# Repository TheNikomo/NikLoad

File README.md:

# Licensing

The hardware design files are covered under Creative Commons Attribution-ShareAlike 4.0 International (CC-BY-SA)

The software will probably end up under GPLv3 - will look into that after hardware exists

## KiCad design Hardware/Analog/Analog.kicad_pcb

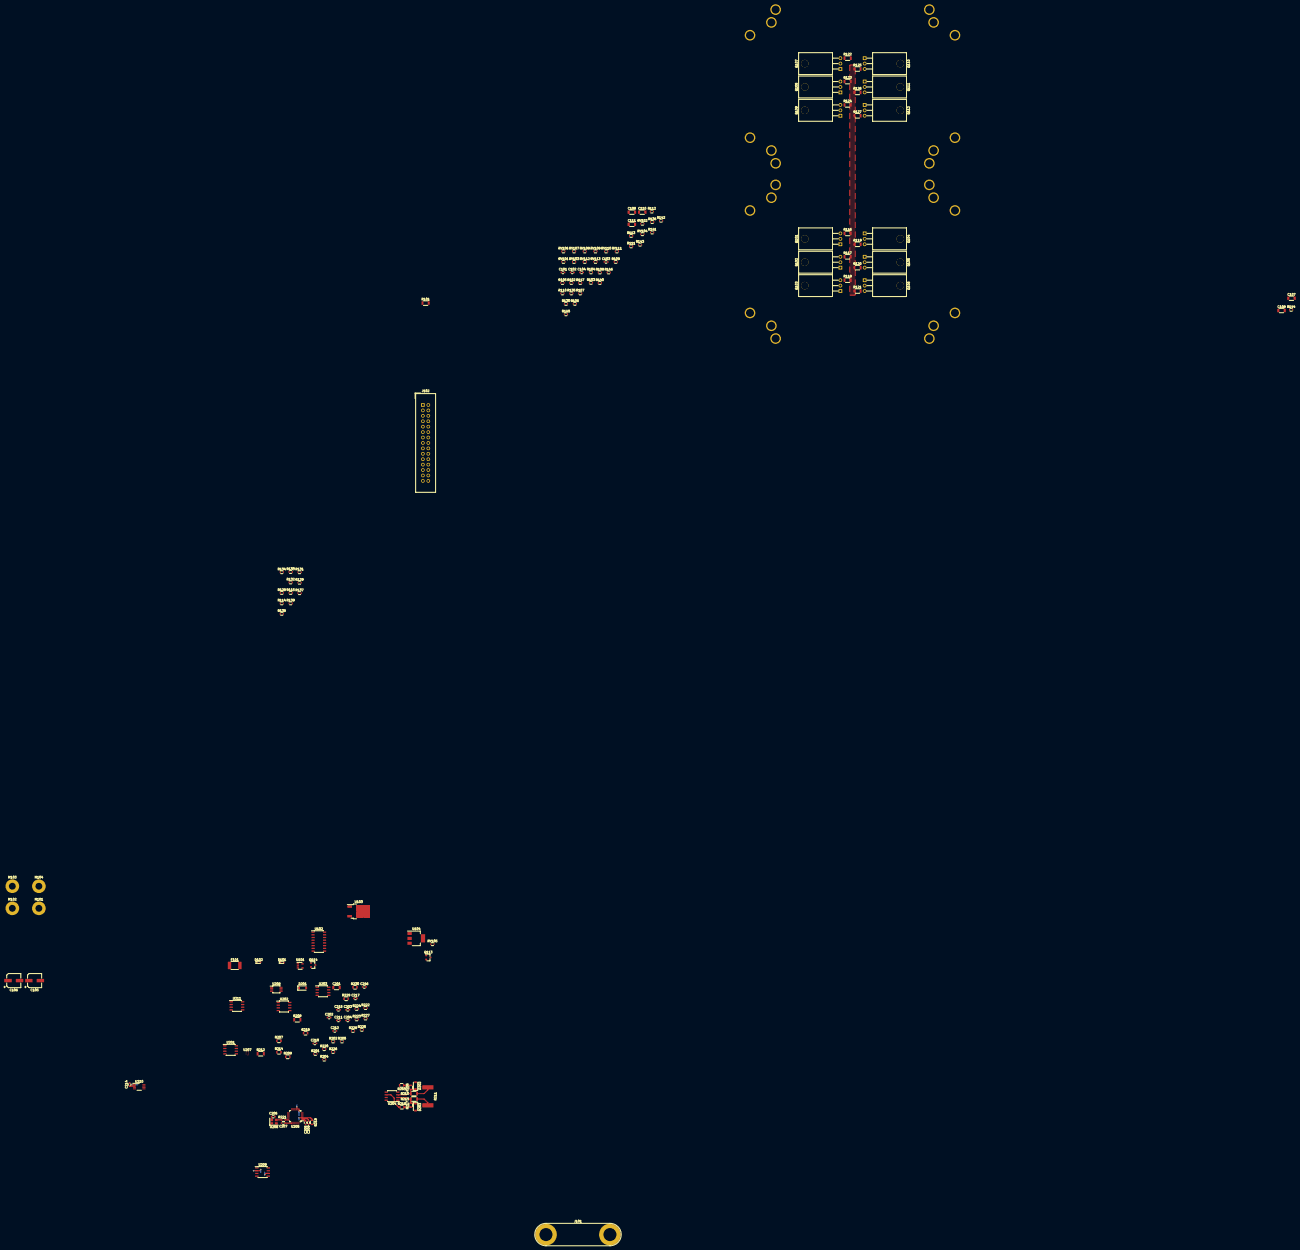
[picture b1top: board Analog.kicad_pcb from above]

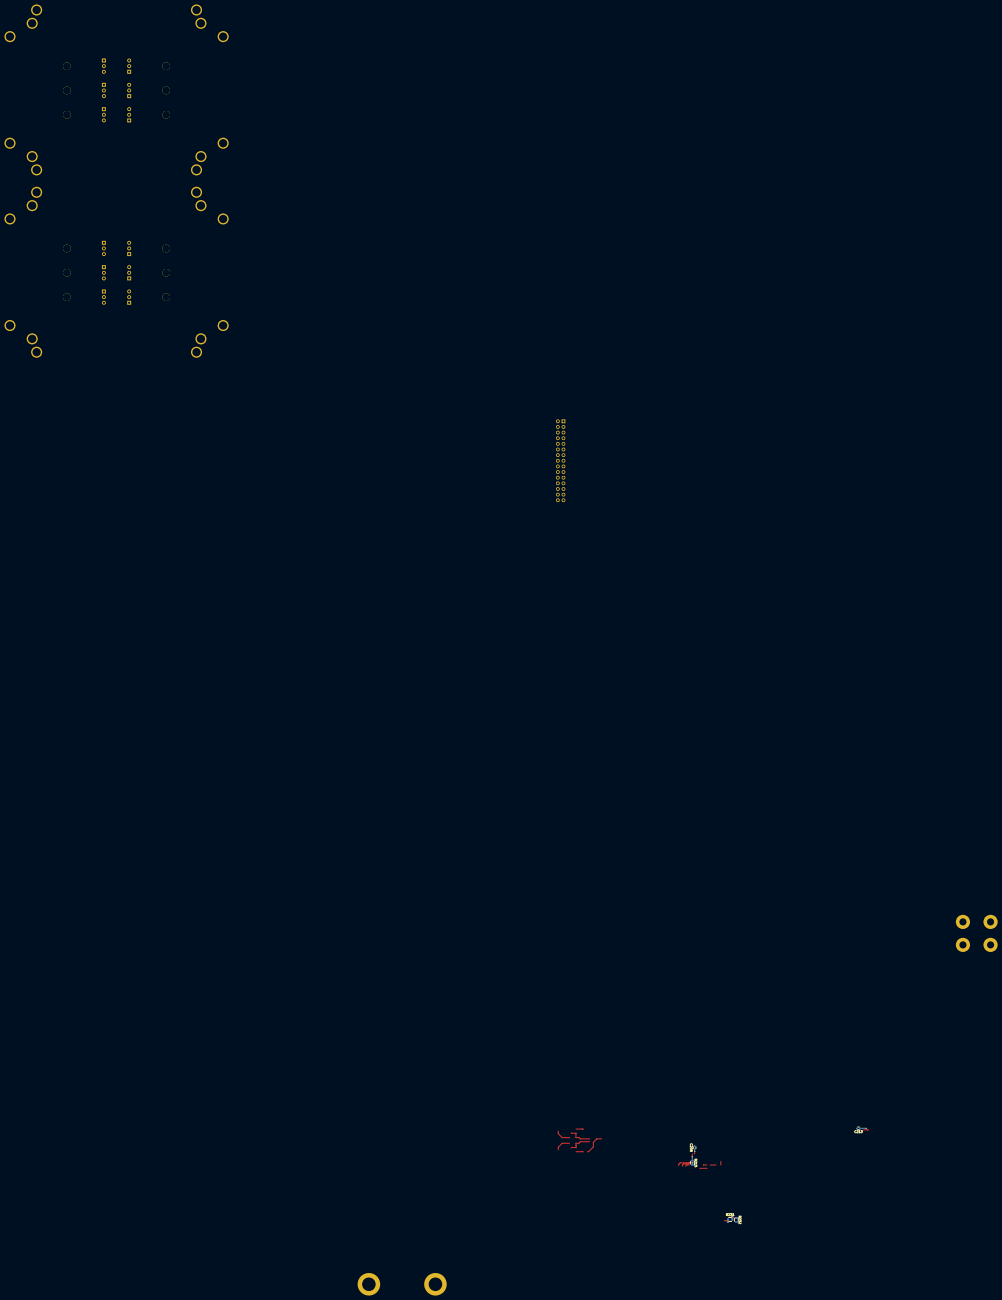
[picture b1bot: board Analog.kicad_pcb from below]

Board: 2 copper layers, 161 parts (5 on the bottom side), 112 nets.

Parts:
C101, C104, C206, C210, C211, C212, C213, C214, C215, C216, C217: 0.1µF; C_0603
C102, C202, C203, C204, C205, C207, C208, C209: 1µF; C_0603
C103: 100pF; C_0603
C105, C106: 150µF; CP_Elec_6.3x7.7
C107, C108, C109, C110, C111, C201: 10µF; C_1206
D101, D102: APG1608ZGCK; LED_0603
D201, D202, D203: BAT46WQ-7-F; D_SOD-123
F101: 16V 1.1A 1812; R_1812
J101: Pomona 4mm 30A connector; Banana_Jack_2Pin
J102: 02x15 IDC; IDC-Header_2x15_P2.54mm_Vertical
M101, M102, M103, M104: MOUNTING_HOLE; MountingHole_3.2mm_M3_Pad
Q101, Q102, Q103, Q104, Q105, Q106, Q107, Q108, Q109, Q110, Q111, Q112: PHP23NQ11T; TO-220_Horizontal
Q113, Q114: 2N7002; SOT-23
R101, R210, R213: 1k; R_1206
R102, R103, R104, R105, R106, R107, R108, R109, R110, R111, R112, R113, R146, R147: 100; R_0603
R114: 100k; R_0603
R115, R128, R129, R130, R131, R132, R133, R134, R135, R144, R145, R221: 33; R_0603
R116, R117, R118, R119, R120, R121, R122, R123, R124, R125, R126, R127: 0R02; R_1206
R136, R137, R138, R139, R140, R141, R142, R143, R201, R202, R204, R205, R222, R223, R224, R226, R227, R228: 51k1; R_0603
R203, R206, R207, R209, R214, R215, R216, R217, R218, R219, R229, R230, R231, R232: 20k; R_0805
R208: 990k; R_1206
R211: 2mOhm; R_3920
R212: 41.2k; R_1206
R220: 10k; R_0603
R225: 60k4; R_0603
RV101, RV102, RV103, RV104, RV105, RV106, RV107, RV108, RV109, RV110, RV111, RV112, RV113: 5V; R_0603
U101: OPA180; SOT-23-5
U102: 74HC595; SOIC-16_3.9x9.9mm_Pitch1.27mm
U103: NCP1117DT50G; TO-252-2
U104: SPX1117-33; SOT-223-3_TabPin2
U201, U202, U203, U204, U209: OPA388; SOIC-8_3.9x4.9mm_Pitch1.27mm
U205: ADS127L01; LQFP-32_5x5mm_Pitch0.5mm
U206: TXETCLSANF-16.384MHz; Crystal_SMD_3225-4pin_3.2x2.5mm
U207: NX3L4357
U208: MCP4921T-E/MS; MSOP-8_3x3mm_Pitch0.65mm
U210: DAC8560; VSSOP-8_3.0x3.0mm_Pitch0.65mm
U211: MAX6126AASA25+; SOIC-8_3.9x4.9mm_Pitch1.27mm

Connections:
+3V3: C104.1, C111.1, C202.1, C203.1, C204.1, C206.1, C210.1, C212.1, C213.1, R136.1, R138.1, R140.1, R142.1, R201.1, R202.2, U102.10, U102.16, U104.2, U205.6, U205.27, U205.32, U206.4, U207.10, U208.1, U210.1
+5V: C109.1, C110.1, R146.2, R147.2, U103.2, U104.3, U201.7, U202.7, U203.7, U204.7, U209.7
+12V: C101.1, C102.1, C105.1, C106.1, C107.1, C108.1, C215.1, F101.1, U101.5, U103.3, U211.2
/CurrentSense: R216.1, R229.2, U101.3, U204.6
/DUT+: J101.1, Q101.2, Q101.4, Q102.2, Q102.4, Q103.2, Q103.4, Q104.2, Q104.4, Q105.2, Q105.4, Q106.2, Q106.4, Q107.2, Q107.4, Q108.2, Q108.4, Q109.2, Q109.4, Q110.2, Q110.4, Q111.2, Q111.4, Q112.2, Q112.4, R208.1
/Measurement/ADC_INPUT: U205.4, U207.3
/Measurement/DAC8560: U207.8, U209.3, U210.3, U210.4
/Measurement/DUT-: J101.2, R211.2, R212.2, R213.1
/Measurement/FILTER0: R137.1, U205.13
/Measurement/FILTER1: R139.2, U205.12
/Measurement/OSR0: R141.2, U205.16
/Measurement/OSR1: R143.2, U205.15
/Measurement/Offset_DAC: C211.1, U201.3, U202.3, U208.8
/Measurement/Offset_LDAC: R145.1, RV110.1, U208.5
/Measurement/S0: U102.4, U207.1
/Measurement/S1: U102.5, U207.2
/Measurement/SPI0_CE0: R132.1, RV104.1, U205.23
/Measurement/SPI0_CLK: R130.1, RV101.1, U205.22
/Measurement/SPI0_MISO: R128.2, U205.20
/Measurement/SPI0_MOSI: R131.1, RV102.1, U205.21
/Measurement/SPI1_CE0: R135.1, RV108.1, U210.5
/Measurement/SPI1_CE1: R144.1, RV109.1, U208.2
/Measurement/SPI1_CLK: R133.1, RV106.1, U208.3, U210.6
/Measurement/SPI1_MOSI: R134.1, RV107.1, U208.4, U210.7
/Measurement/SenseResistor: R116.2, R117.2, R118.2, R119.2, R120.2, R121.2, R122.2, R123.2, R124.2, R125.2, R126.2, R127.2, R210.2, R211.1
/Measurement/VoltageSense: R214.1, U203.6, U207.9
/Measurement/Vref: C201.2, C214.1, C217.1, R215.2, U205.9, U208.6, U210.2, U211.6, U211.7
/Measurement/~DRDY~/FSYNC: R129.2, U205.19
/Setpoint: R101.1, R231.1, U209.6
Earth: C101.2, C102.2, C104.2, C105.2, C106.2, C107.2, C108.2, C109.2, C110.2, C111.2, C201.1, C202.2, C203.2, C204.2, C205.2, C206.2, C207.2, C208.2, C209.2, C210.2, C211.2, C212.2, C213.2, C214.2, C215.2, C216.2, C217.2, D201.2, D202.2, D203.2, J102.2, J102.4, J102.6, J102.8, J102.10, J102.12, J102.14, J102.16, J102.18, J102.20, J102.22, J102.24, J102.26, J102.28, J102.30, M101.1, M102.1, M103.1, M104.1, Q113.2, Q114.2, R114.2, R218.2, R219.2, R220.2, R225.2, R226.1, R227.1, R228.1, R230.1, R232.2, RV101.2, RV102.2, RV103.2, RV104.2, RV105.2, RV106.2, RV107.2, RV108.2, RV109.2, RV110.2, RV111.2, RV112.2, RV113.2, U101.2, U102.8, U102.13, U103.1, U104.1, U201.4, U202.4, U203.4, U204.4, U205.5, U205.10, U205.18, U205.26, U205.31, U206.2, U207.4, U207.5, U208.7, U209.4, U210.8, U211.3, U211.4
unnamed: C103.1, R115.1
unnamed: C103.2, R102.2, R103.2, R104.2, R105.2, R106.2, R107.2, R108.2, R109.2, R110.2, R111.2, R112.2, R113.2, R114.1, U101.1
unnamed: C205.1, U205.1
unnamed: C207.1, U205.25
unnamed: C208.1, U205.11
unnamed: C209.1, U205.2
unnamed: C216.1, U211.1
unnamed: D101.1, Q113.3
unnamed: D101.2, R146.1
unnamed: D102.1, Q114.3
unnamed: D102.2, R147.1
unnamed: D201.1, R207.2, R209.2, U203.3
unnamed: D202.1, R206.1, R210.1, U204.3
unnamed: D203.1, R213.2, R217.2, U204.2
unnamed: F101.2, J102.1, J102.3
unnamed: J102.5, R130.2
unnamed: J102.7, R131.2
unnamed: J102.9, R128.1, RV103.1
unnamed: J102.11, R132.2
unnamed: J102.13, R129.1, RV105.1
unnamed: J102.15, R133.2
unnamed: J102.17, R134.2
unnamed: J102.19, R135.2
unnamed: J102.21, R144.2
unnamed: J102.23, R145.2
unnamed: J102.25, RV113.1, U102.11
unnamed: J102.27, RV112.1, U102.14
unnamed: J102.29, RV111.1, U102.12
unnamed: Q101.1, R102.1
unnamed: Q101.3, R116.1
unnamed: Q102.1, R103.1
unnamed: Q102.3, R117.1
unnamed: Q103.1, R104.1
unnamed: Q103.3, R118.1
unnamed: Q104.1, R105.1
unnamed: Q104.3, R119.1
unnamed: Q105.1, R106.1
unnamed: Q105.3, R120.1
unnamed: Q106.1, R107.1
unnamed: Q106.3, R121.1
unnamed: Q107.1, R108.1
unnamed: Q107.3, R122.1
unnamed: Q108.1, R109.1
unnamed: Q108.3, R123.1
unnamed: Q109.1, R110.1
unnamed: Q109.3, R124.1
unnamed: Q110.1, R111.1
unnamed: Q110.3, R125.1
unnamed: Q111.1, R112.1
unnamed: Q111.3, R126.1
unnamed: Q112.1, R113.1
unnamed: Q112.3, R127.1
unnamed: Q113.1, U102.6
unnamed: Q114.1, U102.7
unnamed: R101.2, R115.2, U101.4
unnamed: R136.2, R137.2, U102.15
unnamed: R138.2, R139.1, U102.1
unnamed: R140.2, R141.1, U102.2
unnamed: R142.2, R143.1, U102.3
unnamed: R201.2, R204.2
unnamed: R202.1, R205.1
unnamed: R203.1, R206.2
unnamed: R203.2, U202.2, U202.6
unnamed: R204.1, U205.29
unnamed: R205.2, U205.28
unnamed: R207.1, U201.2, U201.6
unnamed: R208.2, R209.1, R212.1
unnamed: R214.2, R218.1, U203.2
unnamed: R215.1, R219.1, U205.3
unnamed: R216.2, R217.1
unnamed: R220.1, U205.8
unnamed: R221.1, U206.3
unnamed: R221.2, U205.24
unnamed: R222.1, R226.2
unnamed: R222.2, U205.14
unnamed: R223.1, R227.2
unnamed: R223.2, U205.17
unnamed: R224.1, R228.2
unnamed: R224.2, U205.30
unnamed: R225.1, U205.7
unnamed: R229.1, R230.2, U207.7
unnamed: R231.2, R232.1, U209.2

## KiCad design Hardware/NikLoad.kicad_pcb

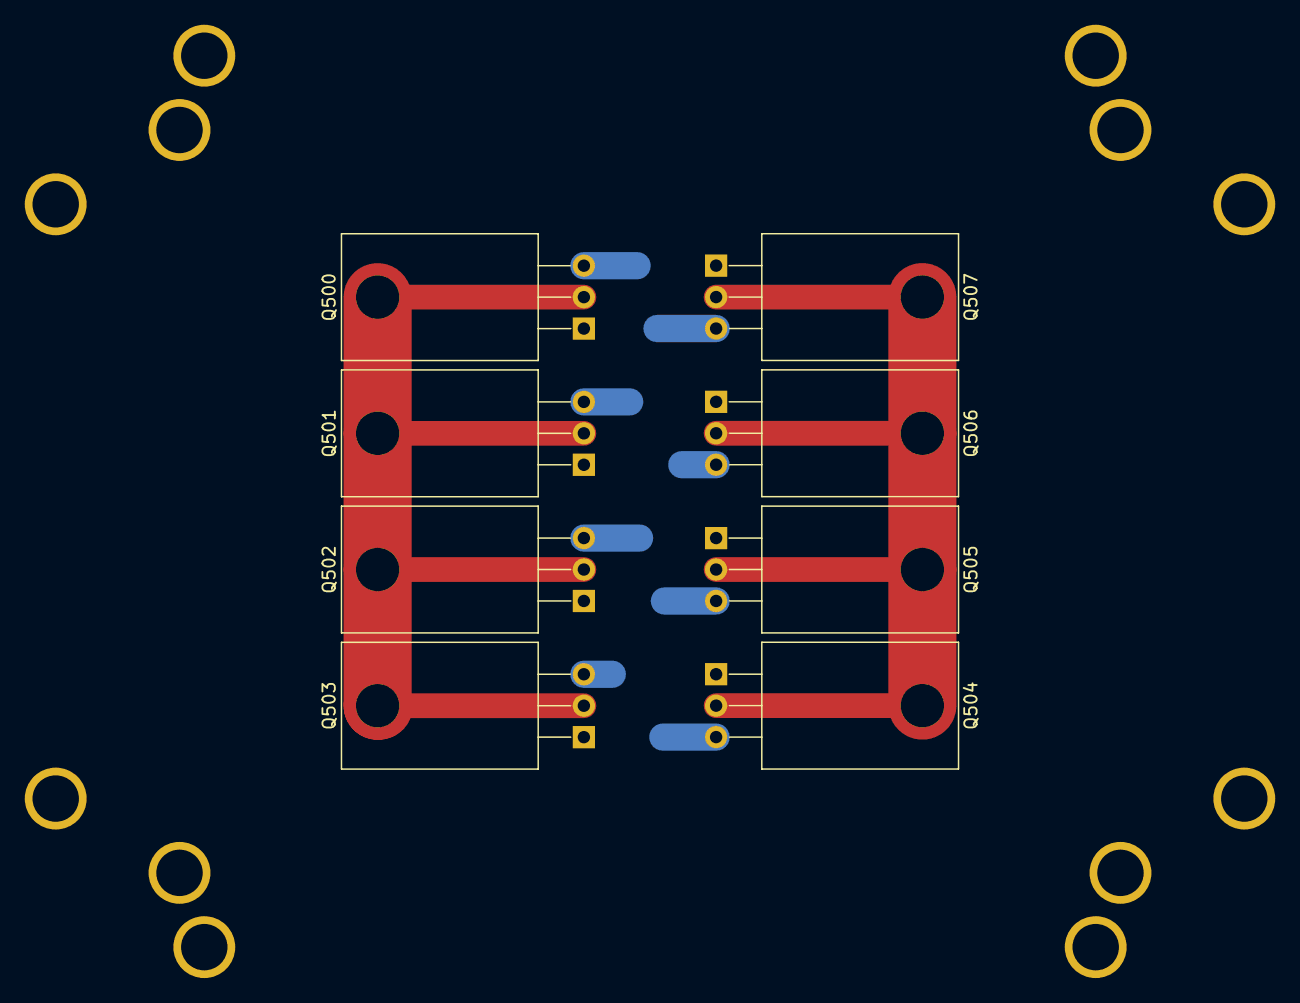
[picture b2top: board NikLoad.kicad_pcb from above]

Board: 2 copper layers, 8 parts (0 on the bottom side), 2 nets.

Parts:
Q500, Q501, Q502, Q503, Q504, Q505, Q506, Q507: IRFZ24NPbF; TO-220_Horizontal

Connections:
CURRENT_SENSE+: Q500.3, Q501.3, Q502.3, Q503.3, Q504.3, Q505.3, Q506.3, Q507.3
DUT+: Q500.2, Q500.4, Q501.2, Q501.4, Q502.2, Q502.4, Q503.2, Q503.4, Q504.2, Q504.4, Q505.2, Q505.4, Q506.2, Q506.4, Q507.2, Q507.4

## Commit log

2017-08-29 Add README
2017-08-29 Add footprint for PC cooling solutions
2017-09-08 Add TO-220 footprint to project
2017-09-08 Add load FETs to schematic and board
2017-09-14 Add notes on analog control and current sense resistors
2017-09-16 Add datasheet for current sense op amp
2017-09-16 Add spreadsheet for current sense calcs
2017-10-10 Change sense calculation spreadsheet to reflect differential amplifier configuration with an offset
2017-10-10 Update notes to document system design
2017-10-20 Add info on DAC and ADC
2017-10-20 Update sense value spreadsheet to reflect changes made due to DAC selection
2017-10-20 Add current sense
2017-10-26 Change sense_calculations.xlsx
    Git says it's been modified. I have no idea what I've done.
    I'm too lazy to check it out.
2017-10-26 Change load schematic
    Moving measurements over to a separate sheet
2017-10-26 Preliminary measurement setup
    Deleted net file, not yet needed.
    Added preliminary measurement stuff.
    Still need DAC for the offset voltage, and need to find a new ADC.
    Also, doing isolation. Analog board will have +12V in, isolate power on board.
    Isolated 2 channels of SPI between digital and analog.
    Also, add a bunch of files I forgot to add to git. Oops.
2017-10-26 Move files to new folder
    Doing analog and digital boards in two project folders,
    because KiCad can't do more than 1 PCB in a project.
2017-10-26 Add notes on software control
2017-10-27 Rename files
2017-10-27 Added information to the schematic sheets
2017-10-27 Add metadata to symbols
    I could have sworn I did this earlier
2017-10-28 Change DAC8560 symbol
    Moved SPI lines up top and VDD near bottom, close to GND
2017-10-28 Implement 5V reference, clean up measurement sheet
    Still need to decide on the ADC.
    Also, think about SPI0/SPI1 allocation real hard.
2017-11-06 Add new parts
2017-11-06 Implement everything
    Gate drive, voltage sense, offset voltage, current set point, 2.5V reference,
    current sense. Just needs isolation, power, and connectors I believe.
2017-11-06 Update notes and make them specific to the analog board
2017-11-06 Add initial notes on the digital side
2017-11-06 Don't need the datasheets folder
2017-11-07 Update voltage measurement resistor
    Old resistors were picked out for 5V input on the ADC, that was cut in half later
2017-11-07 Remove unnecessary passives from gate driver
2017-11-07 Update driver resistors
    Don't want to slow down the drive that much
2017-11-07 Update Analog.dcm
    I have no idea why this file has changed.
2017-11-09 Add power isolation and 12V rail
2017-11-09 Add Digikey order code to setpoint DAC
2017-11-11 Add power rails and clean up some parts of schematic
2017-11-12 Remove unused label
    Ended up not being used
2017-11-12 Add connector symbol
    No footprint in mind yet, need to look around.
2017-11-13 Preparations for adding isolation and connectors
    Created new hierarchical sheet for isolation parts and board-to-board
    connectors.
    ADS127L01 datasheet specifies setting pins must be pulled to DVDD/DGND
    through 100kOhm resistors - using 49.9K resistors and controlling
    NMOS to DGND through the isolation.
2017-11-13 Add power to the ADC
    I apparently forgot to add that. Good thing I caught it now.
    Would have been caught in PCB layout, and possibly schematic ERC,
    but good thing I spotted it now.
2017-11-15 Add BOM optimization reminder
2017-11-15 Add isolation to data lines, change power symbols
    Found a way to optimize out the READY signal on the ADC. Can send SPI command
    to start conversion instead of toggling a pin.
    Changed power symbols - using global labels to avoid hierarchical labels.
    Used 2x ADuM3151 for SPI + misc. isolation.
    Added optocouplers for the last remaining signals.
    Added PDF of current schematic.
2017-11-16 Wire enable pin on optocouplers
2017-11-16 Add preliminary resistor order codes
    Might have missed some, check later
    Also check tolerances on everything
2017-11-16 Change power pin on ADC
    Missed one in 7e519bf
2017-11-16 Add references to components
2017-11-16 Remove unused Excel file
    This went out of date about immediately, and was never updated
2017-11-21 Add part numbers
    Added part numbers to most parts.
    Implemented an analog mux in front of the ADC, to check that the current
    measurement is working fine.
    Still missing connectors (board to board, banana plug)
2017-11-21 Add status indicator LED
    LED controlled by shift register - means the digital board must be functional
    enough to drive the shift register, in order to control the LED.
    Can function as a "board connected and works" light.
2017-11-21 Switch 33R resistors from 5% to 1%
    At this quantity, the price is almost the same.
2017-11-21 Update PDF
    This is not the final revision (missing connectors and still thinking about
    input protection).
2017-11-27 Add protection diodes
2017-11-28 Remove isolation
    Making it eath-referenced instead
2017-11-29 Add passives to prevent oscillation
2017-11-30 Remove redundant regulator
2017-11-30 Add ESD protection to IO lines, add mounting holes
2017-11-30 Remove redundant resistor
    I moved where the 33ohm resistors are placed in schematic, left one in place
    accidentally.
2017-12-01 Remove control op amp input filter
    Not needed, replace with in-out cap so the amp doesn't have max gain.
2017-12-01 Add capacitor from control op amp output to inverting input
    This forms an integrator that slows down the op amp a little,
    preventing oscillation.
2017-12-01 Update schematic PDF
2017-12-01 Add BOM files
    Project only has part numbers for ordering from Digikey right now,
    don't know if that will change.
2017-12-01 Switch out 2 capacitors for cheaper ones
2017-12-01 Fix ERC errors
2017-12-04 Move footprints to their own directory
2017-12-04 Minor BOM optimization
    Removed 100k resistors, used 2 51k1 in series instead
2017-12-04 Adjust compensation on control op amp
2017-12-04 Update plotted schematic files
2017-12-04 BOM optimization
    Simple pulldowns with oddly specific values, but should be fine to swap.
2017-12-07 Add rest of footprints, assign footprints to components
2017-12-07 Update BOM, just in case
2017-12-07 Change one footprint to one that exists
2017-12-07 Update schematic symbol to reflect footprint change
2017-12-11 Position load FETs, heatsink mounts, source resistors
2017-12-11 Fix mistake in MOSFET spacing
2017-12-16 Add footprint for 0.3mm drill via
    Easier to stitch using that
